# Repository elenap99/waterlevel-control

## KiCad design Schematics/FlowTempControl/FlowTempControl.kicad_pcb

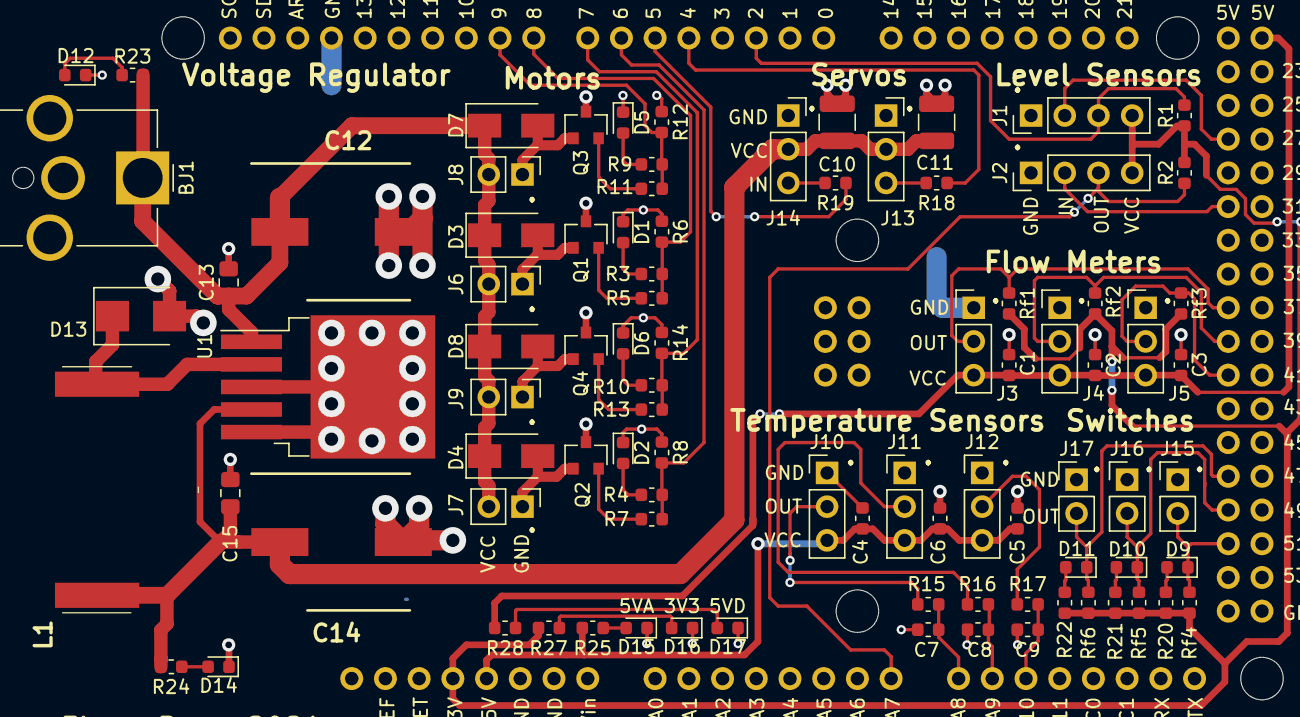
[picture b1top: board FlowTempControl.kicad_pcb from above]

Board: 2 copper layers, 90 parts (0 on the bottom side), 51 nets.

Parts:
BJ1: Barrel_Jack_Switch; BarrelJack_CUI_PJ-063AH_Horizontal_CircularHoles
C1, C2, C3, C4, C5, C6, C7, C8, C9: C; C_0603_1608Metric
C10, C11: C; C_1210_3225Metric
C12, C14: 680uF; CAPAE1030X1050N
C13, C15: C; C_0805_2012Metric_Pad1.15x1.40mm_HandSolder
D1, D2, D9, D10, D11, D12, D14, D15, D16, D17: LED; LED_0603_1608Metric
D3, D4, D7, D8: 1N4007; D_SMA
D5, D6: LED; D_0603_1608Metric
D13: SS54BF; D_SMB
J1, J2: PinHeader_1x04_P2.54mm_Vertical
J3, J4, J5, J10, J11, J12: PinHeader_1x03_P2.54mm_Vertical
J6, J7, J8, J9, J15, J16, J17: PinHeader_1x02_P2.54mm_Vertical
J13, J14: PinSocket_1x03_P2.54mm_Vertical
L1: DL50-33; DO5040H334KLD
Q1, Q2, Q3, Q4: Q_NMOS_DGS; SOT-23
R1, R2, R3, R4, R9, R10, R15, R16, R17, R18, R19, R20, R21, R22, R23, R24, R25, R27, R28: R; R_0603_1608Metric
R5, R7, R11, R13: 150; R_0603_1608Metric
R6, R8, R12, R14: 10k; R_0603_1608Metric
Rf1, Rf2, Rf3, Rf4, Rf5, Rf6: 10K; R_0603_1608Metric
U1: LM2596S-5; TO-263-5_TabPin3
XA1: Arduino_Due_Shield

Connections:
5Vp: C10.2, C11.2, C14.1, C15.1, J13.2, J14.2, L1.2, R24.1, U1.4
+3V3: J1.4, J2.4, R1.2, R2.2, R20.2, R21.2, R22.2, R27.2, Rf1.2, Rf2.2, Rf3.2, Rf4.2, Rf5.2, Rf6.2, XA1.3V3
+5VA: C4.2, C5.2, C6.2, J10.3, J11.3, J12.3, R25.2, XA1.5V1
+5VD: C1.2, C2.2, C3.2, J3.3, J4.3, J5.3, R28.2, XA1.5V4
Fin1: J3.2, Rf1.1, XA1.D36
Fin2: J4.2, Rf2.1, XA1.D38
Fin3: J5.2, Rf3.1, XA1.D40
GND: BJ1.2, C1.1, C2.1, C3.1, C4.1, C5.1, C6.1, C7.2, C8.2, C9.2, C10.1, C11.1, C12.2, C13.2, C14.2, C15.2, D1.1, D2.1, D5.1, D6.1, D12.1, D13.2, D14.1, D15.1, D16.1, D17.1, J1.1, J2.1, J3.1, J4.1, J5.1, J10.1, J11.1, J12.1, J13.1, J14.1, J15.1, J16.1, J17.1, Q1.3, Q2.3, Q3.3, Q4.3, R6.1, R8.1, R12.1, R14.1, U1.3, U1.5, XA1.GND1, XA1.GND2, XA1.GND3, XA1.GND5, XA1.GND6
Lin1: J1.3, R1.1, XA1.D2
Lin2: J2.3, R2.1, XA1.A7
Mout1: R18.1, XA1.D4
Mout2: R19.1, XA1.D5
unnamed: D1.2, R3.2
unnamed: D2.2, R4.2
unnamed: D3.2, J6.1, Q1.1
unnamed: D4.2, J7.1, Q2.1
unnamed: D5.2, R9.2
unnamed: D6.2, R10.2
unnamed: D7.2, J8.1, Q3.1
unnamed: D8.2, J9.1, Q4.1
unnamed: D9.2, R20.1
unnamed: D10.2, R21.1
unnamed: D11.2, R22.1
unnamed: D12.2, R23.2
unnamed: D13.1, L1.1, U1.2
unnamed: D14.2, R24.2
unnamed: D15.2, R25.1
unnamed: D16.2, R27.1
unnamed: D17.2, R28.1
unnamed: J10.2, R15.2
unnamed: J11.2, R16.2
unnamed: J12.2, R17.2
unnamed: J13.3, R18.2
unnamed: J14.3, R19.2
unnamed: Q1.2, R5.1
unnamed: Q2.2, R7.1
unnamed: Q3.2, R11.1
unnamed: Q4.2, R13.1
Pout1: R3.1, R5.2, R6.2, XA1.D8
Rout1: R9.1, R11.2, R12.2, XA1.D9
SWin1: D9.1, J15.2, Rf4.1, XA1.D50
SWin2: D10.1, J16.2, Rf5.1, XA1.D48
SWin3: D11.1, J17.2, Rf6.1, XA1.D46
Tin1: C7.1, R15.1, XA1.A8
Tin2: C8.1, R16.1, XA1.A9
Tin3: C9.1, R17.1, XA1.A10
Vcc: BJ1.1, C12.1, C13.1, D3.1, D4.1, D7.1, D8.1, J6.2, J7.2, J8.2, J9.2, R23.1, U1.1
Vout1: R4.1, R7.2, R8.2, XA1.D6
Vout2: R10.1, R13.2, R14.2, XA1.D7
chargePin1: J1.2, XA1.D26
chargePin2: J2.2, XA1.D30

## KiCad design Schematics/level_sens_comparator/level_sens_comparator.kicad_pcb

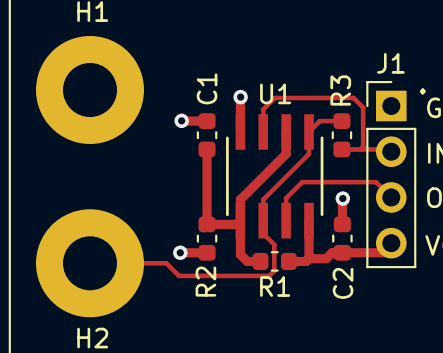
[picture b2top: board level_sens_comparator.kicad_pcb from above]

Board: 2 copper layers, 9 parts (0 on the bottom side), 6 nets.

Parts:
C1, C2: C; C_0603_1608Metric
H1, H2: MountingHole_3mm_Pad
J1: PinHeader_1x04_P2.54mm_Vertical
R1: 36K; R_0603_1608Metric
R2: 63K; R_0603_1608Metric
R3: 100K; R_0603_1608Metric
U1: TS372IDT

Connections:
/OUT: J1.3, U1.7
/chargePin: J1.2, R3.1, U1.3
GND: C1.2, C2.2, H1.1, J1.1, R2.2, U1.4
unnamed: H2.1, R3.2, U1.1, U1.6
VCC: C2.1, J1.4, R1.1, U1.8
Vref: C1.1, R1.2, R2.1, U1.2, U1.5

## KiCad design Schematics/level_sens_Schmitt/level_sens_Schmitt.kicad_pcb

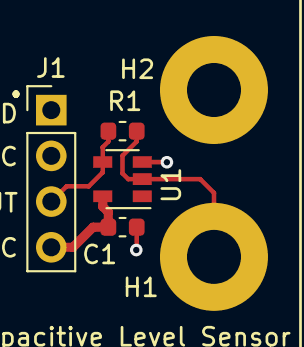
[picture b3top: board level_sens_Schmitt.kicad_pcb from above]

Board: 2 copper layers, 6 parts (0 on the bottom side), 4 nets.

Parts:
C1: C; C_0603_1608Metric
H1, H2: MountingHole_3mm_Pad
J1: PinHeader_1x04_P2.54mm_Vertical
R1: R; R_0603_1608Metric
U1: SOT-23-5

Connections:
GND: C1.2, H2.1, J1.1, U1.3
unnamed: H1.1, R1.2, U1.2
unnamed: J1.3, R1.1, U1.4
VCC: C1.1, J1.4, U1.5

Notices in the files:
parts and their libraries:
Copyright 2016 Accelerated Designs. All rights reserved.
